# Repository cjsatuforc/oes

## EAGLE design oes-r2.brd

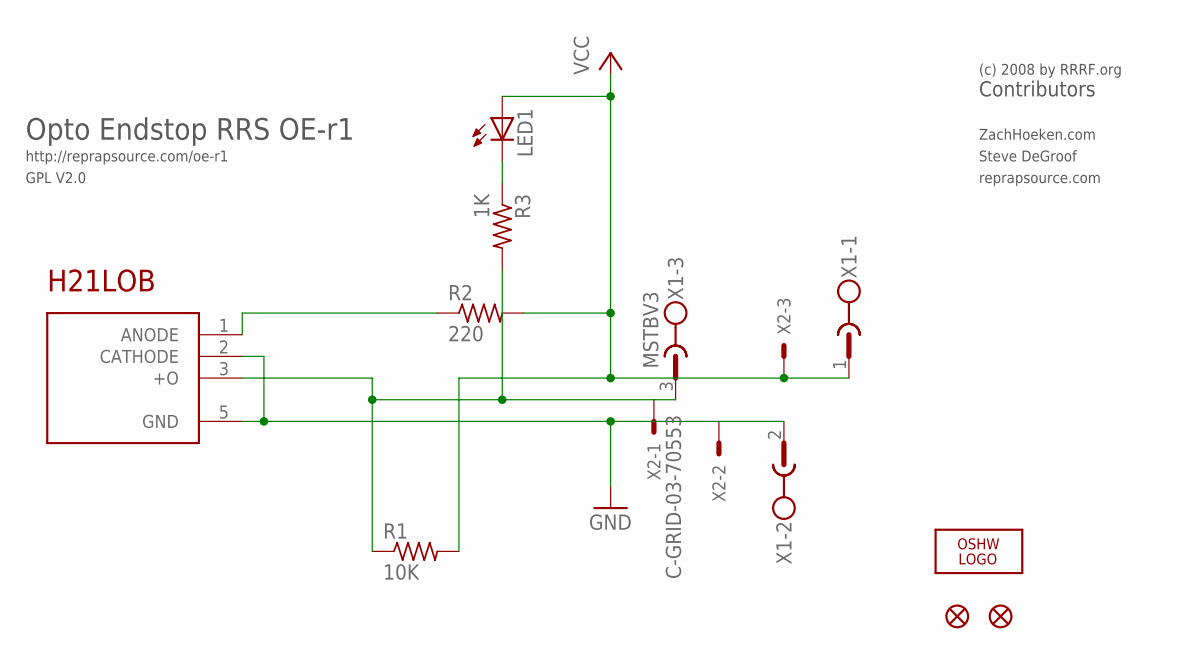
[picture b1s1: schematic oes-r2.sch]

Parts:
JP1, JP2: FIDUCIAL1X2; FIDUCIAL-1X2
LED1: LEDCHIP-LED0805; CHIP-LED0805
LOGO1: OSHW_LOGO_6MILX0100-NT; OSHW_6X100_NOTEXT
R1: 10K; R0603
R2: 220; R0603
R3: 1K; R0603
U1: H21LOB; H21
X1: MSTBV3
X2: C-GRID-03-70553; 70553-03

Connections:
GND: U1.2 (CATHODE), U1.5 (GND), X1.2, X2.2
unnamed: LED1.C, R3.1
unnamed: R1.1, R3.2, U1.3 (+O), X1.3, X2.1
unnamed: R2.1, U1.1 (ANODE)
VCC: LED1.A, R1.2, R2.2, X1.1, X2.3

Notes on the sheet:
Opto Endstop RRS OE-r1
http://reprapsource.com/oe-r1
Contributors
ZachHoeken.com
Steve DeGroof
reprapsource.com
GPL V2.0
(c) 2008 by RRRF.org

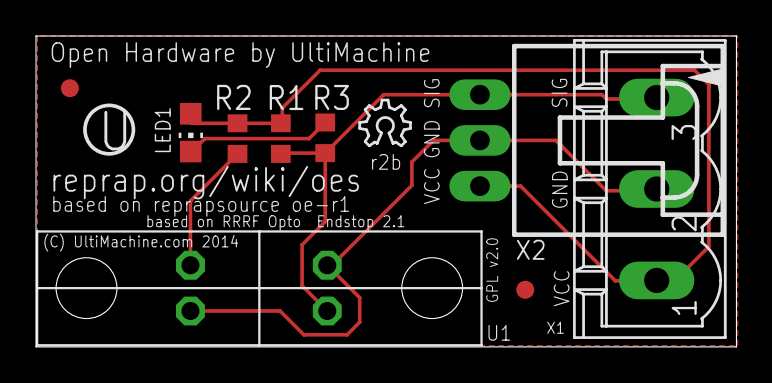
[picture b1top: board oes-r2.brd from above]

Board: 2 copper layers, 38.9 x 17.3 mm, 10 parts (0 on the bottom side), 5 nets.

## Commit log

2017-02-24 init
